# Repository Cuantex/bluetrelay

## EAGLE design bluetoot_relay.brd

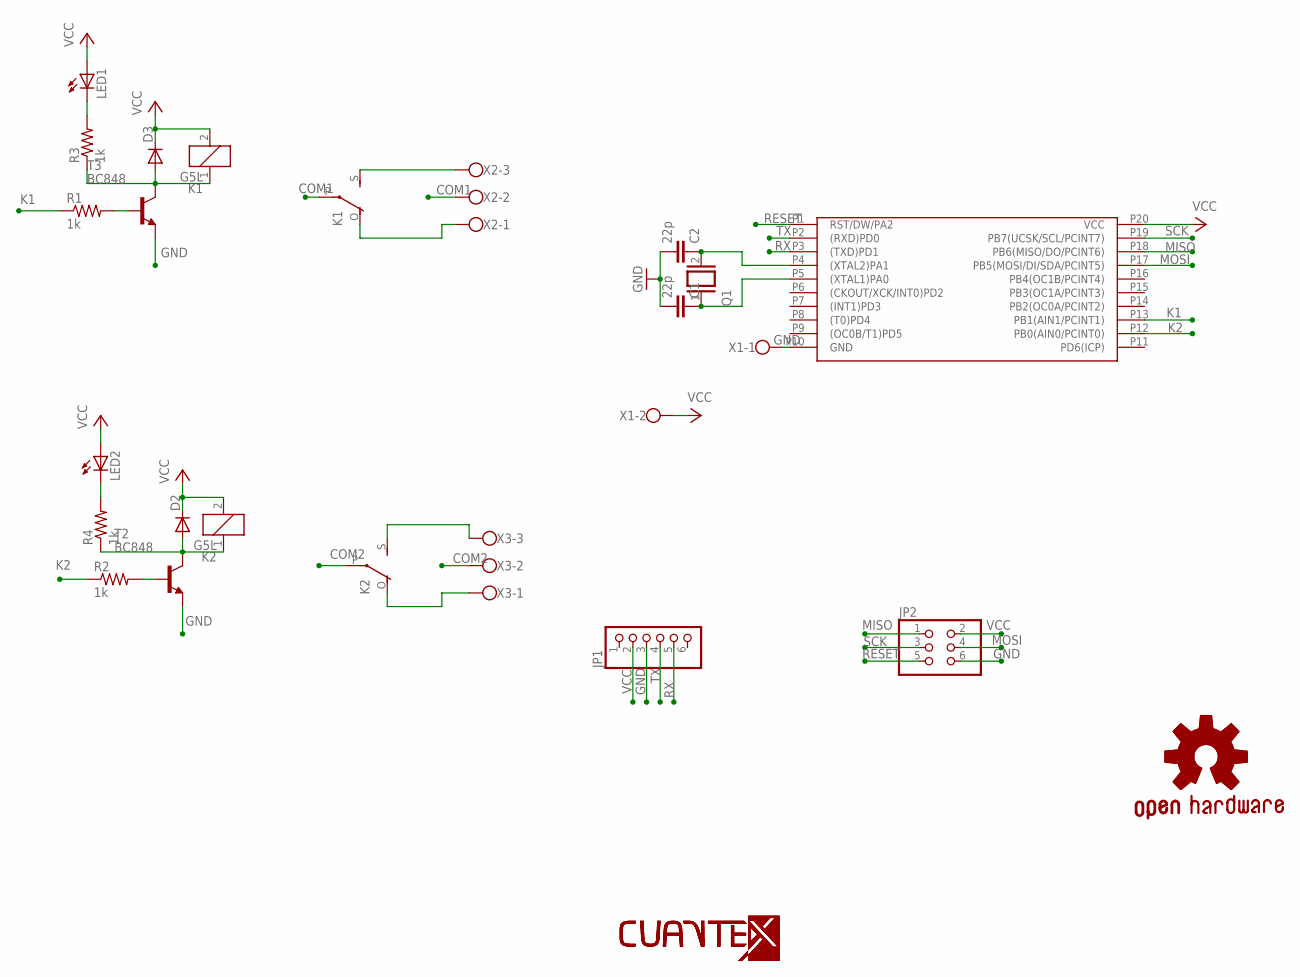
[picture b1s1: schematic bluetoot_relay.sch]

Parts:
C1, C2: 22p; C0603
D2, D3: DIODE-SMB; SMB
GOLD_ORB_SM1: OSHWLOGO_GOLD_ORB_SM; OSHW2
JP1: PINHD-1X6; 1X06
JP2: PINHD-2X3; 2X03
K1, K2: G5L; G5LE
LED1, LED2: LED0603; LED-0603
Q1: XTAL/S; QS
R1, R2, R3, R4: 1k; R0603
T2, T3: BC848; SOT23
U$1: ATTYNY2313/V; SOIC
U$3: LOGO-TOP-20MM; C-0
U$4: LOGO-TOP-50MM; C-3
X1: W237-102
X2, X3: W237-103

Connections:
COM1: K1.P, X2.2
COM2: K2.P, X3.2
GND: C1.2, C2.2, JP1.3, JP2.6, T2.2 (E), T3.2 (E), U$1.P10 (GND), X1.1
K1: R1.1, U$1.P13 (PB1(AIN1/PCINT1))
K2: R2.1, U$1.P12 (PB0(AIN0/PCINT0))
MISO: JP2.1, U$1.P18 (PB6(MISO/DO/PCINT6))
MOSI: JP2.4, U$1.P17 (PB5(MOSI/DI/SDA/PCINT5))
unnamed: C2.1, Q1.2, U$1.P4 ((XTAL2)PA1)
unnamed: C1.1, Q1.1, U$1.P5 ((XTAL1)PA0)
unnamed: K1.S, X2.3
unnamed: K1.O, X2.1
unnamed: K2.S, X3.3
unnamed: D3.A, K1.1, R3.1, T3.3 (C)
unnamed: K2.O, X3.1
unnamed: LED1.C, R3.2
unnamed: R1.2, T3.1 (B)
unnamed: D2.A, K2.1, R4.1, T2.3 (C)
unnamed: R2.2, T2.1 (B)
unnamed: LED2.C, R4.2
RESET: JP2.5, U$1.P1 (RST/DW/PA2)
RX: JP1.5, U$1.P3 ((TXD)PD1)
SCK: JP2.3, U$1.P19 (PB7(UCSK/SCL/PCINT7))
TX: JP1.4, U$1.P2 ((RXD)PD0)
VCC: D2.C, D3.C, JP1.2, JP2.2, K1.2, K2.2, LED1.A, LED2.A, U$1.P20 (VCC), X1.2

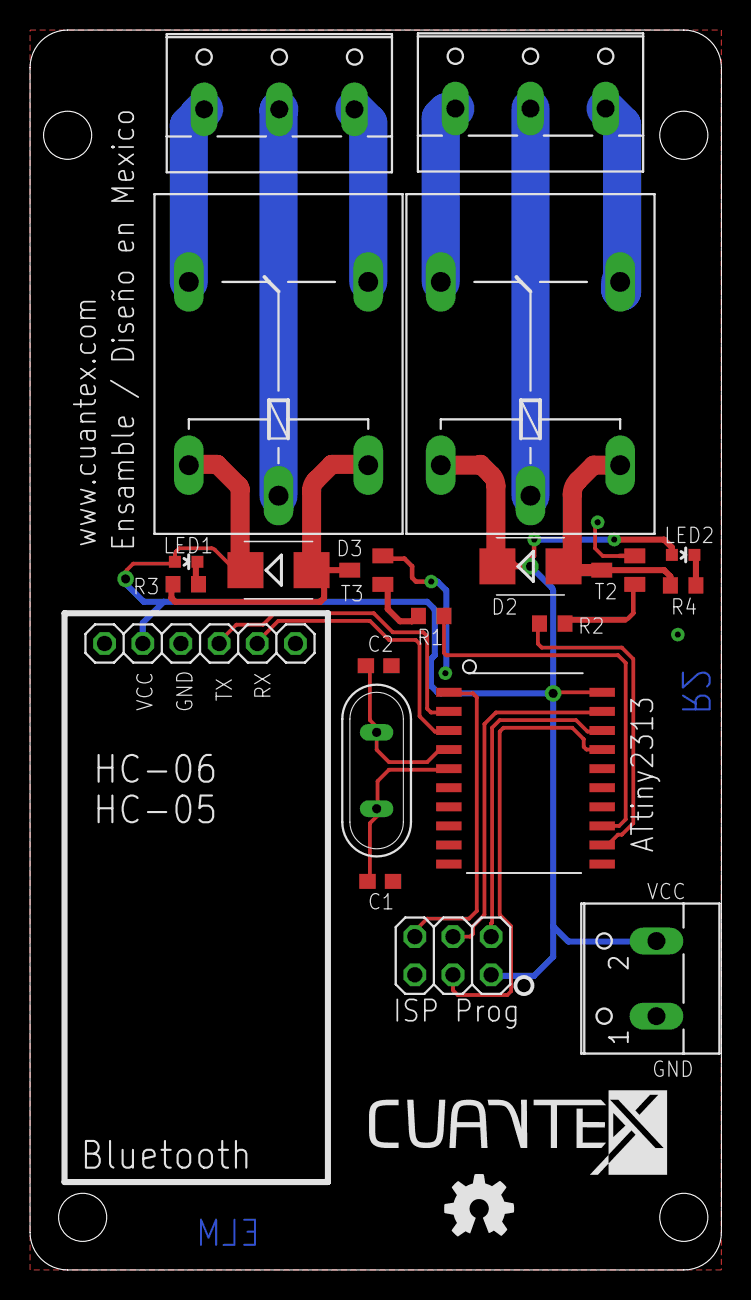
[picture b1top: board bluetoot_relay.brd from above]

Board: 2 copper layers, 46.0 x 82.5 mm, 24 parts (1 on the bottom side), 24 nets.

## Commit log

2016-08-23 Archivos en Git

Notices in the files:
parts and their libraries:
SparkFun: Licensing: CC v3.0 Share-Alike You are welcome to use this library for commercial purposes.
